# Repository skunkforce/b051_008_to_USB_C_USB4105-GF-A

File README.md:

# edgy_board number b051
This design is part of the [edgy board project](https://github.com/skunkforce/edgy_boards). It provides a USB C connector USB4105-GF-A to osf.008 connection. 

# getting started
This repository uses submodules. After cloning use the command 

```$ git submodule update --init --recursive```

to pull the submodules before opening the project with kicad. 

# Tests
Tests can be found in [TESTS.md](TESTS.md)

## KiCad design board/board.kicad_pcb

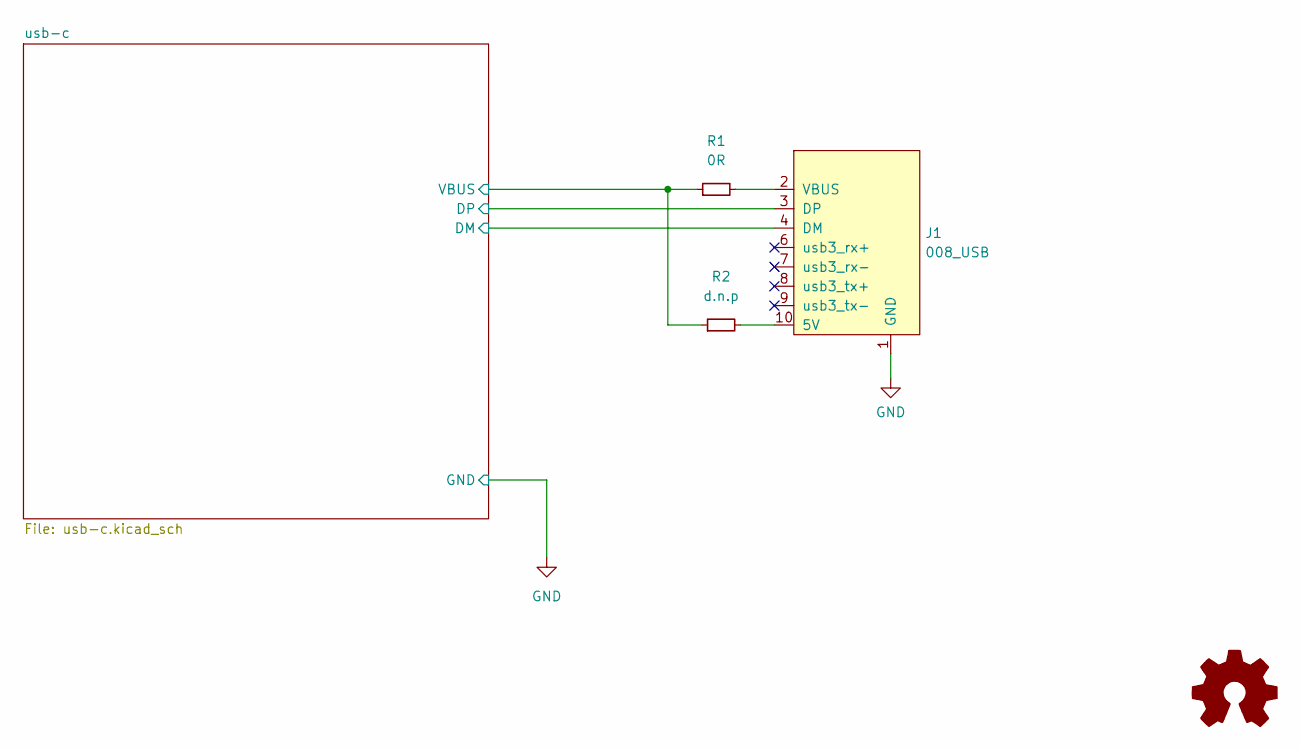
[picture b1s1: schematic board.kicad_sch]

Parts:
J1: 008_USB; on_edge_2x05_host
LOGO1: Logo_Open_Hardware_Small; OSHW-Symbol_6.7x6mm_SilkScreen
R1: 0R; R_0603_1608Metric
R2: d.n.p; R_0603_1608Metric

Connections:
/usb-c/DM: J1.4 (DM); also elsewhere on the board
/usb-c/DP: J1.3 (DP); also elsewhere on the board
/usb-c/VBUS: R1.1, R2.1; also elsewhere on the board
GND: J1.1 (GND); also elsewhere on the board
unnamed: J1.2 (VBUS), R1.2
unnamed: J1.10 (5V), R2.2

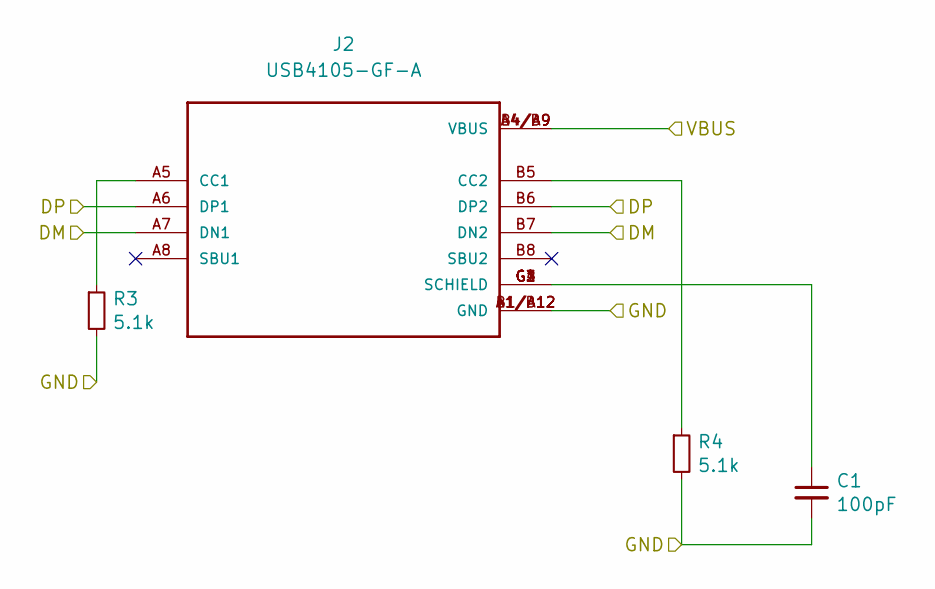
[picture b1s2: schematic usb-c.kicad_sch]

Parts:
C1: 100pF; C_0402_1005Metric
J2: USB4105-GF-A; GCT_USB4105-GF-A
R3, R4: 5.1k; R_0402_1005Metric

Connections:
/usb-c/DM: J2.A7 (DN1), J2.B7 (DN2); also elsewhere on the board
/usb-c/DP: J2.A6 (DP1), J2.B6 (DP2); also elsewhere on the board
/usb-c/VBUS: J2.A4/B9 (VBUS), J2.B4/A9 (VBUS); also elsewhere on the board
GND: C1.2, J2.A1/B12 (GND), J2.B1/A12 (GND), R3.2, R4.2; also elsewhere on the board
unnamed: J2.A5 (CC1), R3.1
unnamed: J2.B5 (CC2), R4.1
unnamed: C1.1, J2.G1 (SCHIELD), J2.G2 (SCHIELD), J2.G3 (SCHIELD), J2.G4 (SCHIELD)

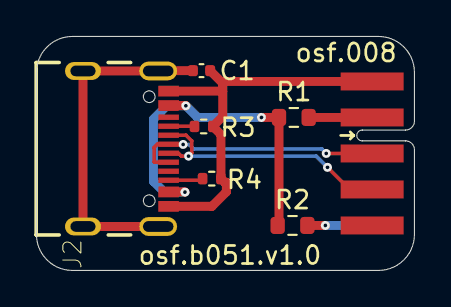
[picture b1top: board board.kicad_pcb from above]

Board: 2 copper layers, 21.0 x 13.0 mm, 8 parts (1 on the bottom side), 9 nets.

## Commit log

2023-03-14 initial
